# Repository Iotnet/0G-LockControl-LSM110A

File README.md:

# 0G LockControl — Alarma IoT dual (acelerómetro + magnético)

> Alarma inalámbrica compacta con detección de movimiento y apertura de puerta/ventana, comunicación Sigfox RC2 sobre el SoC LSM110A.

## Descripción

**0G LockControl** es un dispositivo electrónico autónomo que combina **dos modos de detección de eventos** y los transmite por la red **Sigfox (0G)**:

- **Movimiento / vibración** vía acelerómetro **LIS2DW12** (I²C).
- **Apertura de puerta o ventana** vía sensor magnético — **reed switch NA** o **hall DRV5032** (ambos footprints en la PCB).

El dispositivo es **event-driven**: duerme en modo Stop2 (~3 µA total) y solo despierta por interrupción de hardware. El firmware se ejecuta directamente sobre el **STM32WL** integrado en el LSM110A (firmware API, sin MCU externo).

### Características

- Comunicación **Sigfox RC2** (902-928 MHz, México) — sin WiFi ni red celular.
- Tamaño objetivo **< 5 cm** — instalación adhesiva en interior (oficina, bodega, cuarto frío).
- Batería desechable **CR2450 (3 V, 620 mAh)** + capacitor de soporte 470 µF para pulsos de TX.
- Vida útil estimada de meses a años según frecuencia de eventos.
- Costo reducido de operación y manufactura.

## Arquitectura del sistema

### Ciclo de operación

```
Sleep (3µA)  →  Wake por INT (accel o magnético)  →  Leer sensor
        →  Armar payload 12 bytes  →  TX Sigfox (~50 mA × 2 s)  →  Sleep
```

### Bloques del sistema

<details>
<summary>Ver arquitectura del sistema completo (dispositivo → Sigfox → nube → app)</summary>

</details>

<details>
<summary>Ver diagrama anterior (v1)</summary>

> Diagrama disponible también en formato vectorial: [arquitectura-producto-v1.svg](./docs/Images/arquitectura-producto-v1.svg)

</details>

### Flujo de operación

1. **Detección.** El acelerómetro o el sensor magnético genera una interrupción de hardware.
2. **Despierta.** El LSM110A sale del modo Stop2 vía EXTI.
3. **Lectura.** Se leen sensores (accel via I²C, estado del magnético).
4. **Transmisión.** Se arma el payload de 12 bytes y se envía un mensaje Sigfox.
5. **Entrega.** El backend de Sigfox ejecuta un callback HTTP hacia el servidor de la app.
6. **Notificación.** La app móvil muestra la alerta con timestamp e ID del dispositivo.

## Justificación de arquitectura y cumplimiento normativo

Este dispositivo utiliza el LSM110A con **firmware API** — el código de aplicación corre directamente dentro del STM32WL del módulo, sin MCU externo. Esta es una variante oficial ofrecida por el fabricante SJI.

**¿Por qué no se usa un MCU externo con comandos AT?**
- Menor consumo (un solo MCU en sleep vs dos)
- Menor tamaño (cumple objetivo <5cm)
- Menor costo (~$2-4 USD menos por unidad)
- Menor complejidad de firmware

**¿Se pierden certificaciones?**
No. La certificación Sigfox Verified cubre la capa de RF/protocolo, que es la misma en las versiones AT y API. Para nuestro producto final aplicaremos el enfoque modular de Sigfox Ready, que hereda la conformidad RF del módulo certificado. La FCC del módulo tampoco se afecta mientras no se modifique la capa de radio ni la antena.

Ver documento completo: [docs/arquitectura-justificacion.md](docs/arquitectura-justificacion.md)

### Certificaciones requeridas para comercialización

| Certificación | Qué cubre | Estado |
|---|---|---|
| Sigfox Verified | RF y protocolo del módulo | ✅ Heredada del LSM110A |
| Sigfox Ready | Rendimiento radiado del producto final | ☐ Post-MVP (prueba en lab acreditado) |
| FCC | Radiofrecuencia (USA) | ✅ Heredada del LSM110A (ID: 2AS8LLSM110A) |
| NOM-208 / IFT-008 | Regulación México 902-928 MHz | ☐ Post-MVP (homologación IFT) |

## Componentes principales

| Componente | Parte | Función |
|---|---|---|
| SoC + radio | **LSM110A** (STM32WLE5CC) | MCU Cortex-M4 single-core + radio Sigfox integrado |
| Acelerómetro | **LIS2DW12** (I²C) | Detección de movimiento, INT1 → PA0 |
| Sensor magnético A | **Reed switch NA** | Detección de apertura (opción A) |
| Sensor magnético B | **DRV5032** (hall) | Detección de apertura (opción B) |
| Batería | **CR2450** (3 V, 620 mAh) | Alimentación desechable |
| Cap. soporte | 470 µF electrolítico | Soporte para el pulso de TX Sigfox |
| LDO (opcional) | **TPS7A02** + bypass 0 Ω | Regulación opcional |
| Antena | Traza PCB 50 Ω | Diseño SJI (certificado FCC) |

## Plataforma de desarrollo

| Herramienta | Uso |
|---|---|
| **STM32CubeIDE** | Desarrollo de firmware (C, bare-metal) |
| **STM32CubeMX** | Configuración de periféricos y clocks |
| **KiCad** | Diseño esquemático y PCB |
| **ST-Link + SWD** | Programación y debug |
| **Sigfox Backend** | Dashboard y callbacks |

## Plan de milestones

| Milestone | Entregable | Semana |
|---|---|---|
| **M0** | Repo + spec + CubeIDE setup | 1-2 |
| **M1** | Esquemático KiCad | 2-5 |
| **M2** | FW en Nucleo (accel + reed + Sigfox) | 2-5 |
| **M3** | PCB layout + gerbers | 5-7 |
| **M4** | Low power validado en Nucleo | 7-8 |
| **M5** | PCB fabricada y ensamblada | 8-11 |
| **M6** | Integración FW en PCB custom | 11-12 |
| **M7** | Prueba de campo | 12 |

> **[Ver dashboard interactivo del plan MVP](https://jdiaznxt.github.io/0G-LockControl-LSM110A/docs/dashboard-mvp.html)** — Gantt con checklist por tarea, clic para expandir detalles.

## Estructura del repositorio

```
0G-LockControl-LSM110A/
├── Hardware/
│   ├── v0-replica-sji/    # Réplica v0 del diseño de referencia SJI
│   │   ├── ESTADO.md              # Estado entre fases: decisiones, deuda, hallazgos
│   │   ├── 00-fuente-de-verdad/   # Datos extraídos del DS/UM, con documento y página
│   │   ├── kicad-lib/             # Símbolo 34 pines + footprint LGA-34 (KiCad)
│   │   ├── 01-energia/            # F2  energía + GATE 2
│   │   ├── 02-esquematico/        # F3  esquemático (bloques/ + export/)
│   │   ├── 03-bom/                # F4  BOM
│   │   ├── 04-antena/             # F5  antena
│   │   ├── 05-layout/             # F6  layout
│   │   ├── 06-fabricacion/        # F7  fabricación
│   │   └── 07-bring-up/           # F7  bring-up (el uplink cierra v0)
│   ├── kicad/             # Proyecto KiCad (esquemático + PCB)
│   ├── Datasheets/        # Hojas de datos de componentes clave
│   ├── Schematic/
│   ├── PCB/
│   └── BOM/
├── Firmware/
│   ├── sdk/               # Fork del SDK de SJI (LSM110A)
│   ├── app/               # Código de aplicación
│   ├── drivers/           # Drivers de sensores I2C
│   ├── src/
│   ├── libs/
│   ├── config/
│   └── tools/
├── 3D-Models/
│   ├── Enclosure/
│   └── Assembly/
├── Tests/
│   ├── Lab/
│   └── Field/
├── App/
│   ├── Mobile/
│   └── Backend/
├── docs/
│   ├── spec-producto.md       # Especificación completa v1.0
│   ├── decisiones-tecnicas.md # Decisiones arquitectónicas (ADRs)
│   ├── pinout-lsm110a.md      # Asignación de pines
│   ├── Architecture/
│   ├── Images/
│   ├── References/
│   └── Guides/
├── .gitignore
└── README.md
```

## Antecedentes del desarrollo

Este proyecto es la evolución del trabajo realizado con la placa **NUCLEO-WL55JC2**, donde se validaron los siguientes hitos:

- Conexión exitosa a la red Sigfox (registro en backend, envío de mensajes).
- Conexión exitosa a LORIOT vía LoRaWAN (validación de stack).
- Implementación de detección de flanco con reed switch.
- Envío de payload Sigfox al detectar apertura.
- Caracterización del microcontrolador y periféricos del STM32WL55.

La transición al **LSM110A** permite pasar de una placa de desarrollo a un SoC integrado, habilitando el diseño de una PCB compacta y de bajo costo para producción. El firmware se programa directamente sobre el STM32WL del módulo (firmware API), sin necesidad de MCU externo ni de comandos AT.

## Protocolos de comunicación

### Sigfox (protocolo principal)

- **Zona:** RCZ2 (México / América Latina).
- **Frecuencia:** 902-928 MHz uplink.
- **Mensajes:** hasta 140 mensajes/día uplink, 4 downlink/día.
- **Payload:** máximo 12 bytes por mensaje.
- **Alcance:** hasta 50 km en zona rural, 3-10 km en zona urbana.
- **Potencia TX:** configurable, default +14 dBm (~50 mA).

### Comunicación local (futuro)

- BLE (Bluetooth Low Energy) para activación y configuración desde la app móvil.

## Documentación adicional

- 📕 **[Especificación de producto v1.0 (PDF)](./docs/References/spec-producto-lsm110a-v1.pdf)
- 📄 [Especificación de producto v1.0 (Markdown)](./docs/spec-producto.md)
- 📄 [Decisiones técnicas (ADRs)](./docs/decisiones-tecnicas.md)
- 📄 [Selección de acelerómetro — comparativa y abastecimiento](./docs/seleccion-acelerometro.md)
- 📄 [Pinout de los 34 pines (fuente de verdad, DS R08 Tabla 5-1-1)](./Hardware/v0-replica-sji/00-fuente-de-verdad/pinout-34-pines.md)
- 📄 [Asignación de pines en v0](./docs/pinout-lsm110a.md)
- 📄 [Estado de la réplica v0 del diseño SJI](./Hardware/v0-replica-sji/ESTADO.md)
- 📄 [Justificación de arquitectura API + certificaciones](./docs/arquitectura-justificacion.md)

## Empresa

**0G IoT Net Solutions** — [iotnet.mx](https://iotnet.mx)

## Desarrollador

**José Francisco Díaz Figueroa** — Embedded Systems R&D Engineer
jdiaz@iotnet.mx

## Referencias

- [Documentación STM32WL Series](https://www.st.com/en/microcontrollers-microprocessors/stm32wl-series.html)
- [Repositorio LSM110A (Support-SJI)](https://github.com/Support-SJI/LSM110A)
- [Sigfox Build — Development](https://build.sigfox.com/development)
- [Sigfox Build — Industrialization](https://build.sigfox.com/industrialization#the-sigfox-credentials)
- [STM32CubeWL GitHub](https://github.com/STMicroelectronics/STM32CubeWL)
- [RF Board Layout Guide (AN5457)](https://www.st.com/resource/en/application_note/dm00660594.pdf)

## Licencia

Por definir.

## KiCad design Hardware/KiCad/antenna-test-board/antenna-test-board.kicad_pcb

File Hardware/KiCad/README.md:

# Antena PCB en KiCad — `ANT_IFA_915MHz_LSM110A`

Diseño en KiCad de la antena IFA ranurada del plano **«1.5 Antenna Dimension»**, para el
0G LockControl (LSM110A, Sigfox RC2/RC4, **902 – 928 MHz**).

> Reconstruida y **verificada píxel a píxel contra el plano oficial** del
> `SJIT_LSM110A_UserManual_Rev1.4`. Esa banda no es una elección: el S11 medido por SJI da
> ≤ −16 dB en 902 – 928 MHz y solo −8.7 dB a 868 MHz, así que **para EU868 hay que
> reajustar**.

Todo se genera desde un único fichero de geometría paramétrica y se verifica con el motor
real de KiCad: **142 comprobaciones, 0 fallos, DRC limpio**.

---

## ⚠️ Aviso de certificación — leer antes de usarlo en producción

Este footprint es un **redibujo**. La certificación modular FCC del LSM110A
(FCC ID `2AS8LLSM110A`) cubre **únicamente el patrón «EVB_LSM ANT» de SJI**.

Dónde estamos, con precisión:

- ✅ **La geometría coincide con el plano oficial de SJI** (User Manual Rev 1.4 § 1.5),
  verificada píxel a píxel sobre el bitmap original: los seis niveles verticales, las dos
  aperturas de ranura, los extremos horizontales y el gap del CPWG. No queda ninguna cota
  en duda.
- ✅ **La red de matching coincide con el esquemático oficial** (§ 1.3): `L101` 0 Ω serie,
  `C101` 2.2 pF shunt lado antena, `C102` DNI shunt lado radio.
- ⚠️ **Lo que el plano no resuelve** es el detalle por debajo de ~0.12 mm: radios de
  esquina y compensaciones de grabado. Para eso sigue haciendo falta el **Gerber**, que es
  confidencial (pedirlo a GREATECH o SJI bajo NDA — ver
  [`certificacion-FCC/README.md`](../certificacion-FCC/README.md)).
- ⚠️ **Para apoyarse en la certificación modular**, la decisión no es de ingeniería sino
  del expediente: hay que confirmar con el certificador si «igual al plano cotado del
  fabricante» basta, o si exige el Gerber. `docs/especificaciones-diseno-pcb.md` pide lo
  segundo: *«Antena importada del Gerber oficial SJI (NO redibujada a mano)»*.
- ✅ **Hay criterio de aceptación eléctrico:** el S11 medido de SJI (§ 1.6) está en
  [`docs/verificacion.md`](docs/verificacion.md#criterio-de-aceptación-de-la-medida). Si la
  placa fabricada reproduce esa curva, el redibujo queda validado también eléctricamente.

---

## Contenido

**Las bibliotecas KiCad NO viven aquí.** Están donde vive el LSM110A, para que KiCad
necesite un solo path registrado y todo salga bajo un único nickname:

```
../v0-replica-sji/kicad-lib/                nickname de footprints: 0G-LockControl
  LSM110A.kicad_mod                         módulo LGA-34            (generado en F1)
  LSM110A.kicad_sym                         símbolo, 34 pines        (generado en F1)
  ANT_IFA_915MHz_LSM110A.kicad_mod          la antena: cobre + keepout + documentación
  ANT_LSM110A_BreakAwaySlots_EVM_ONLY.kicad_mod  troquelado del EVM - NO en el producto
  C_0402_1005Metric_0G.kicad_mod            land 0402 para L101 / C101 / C102
  TP_Coax_50R_NanoVNA.kicad_mod             isla de 3 pads para pigtail coaxial
  0G_Antenna.kicad_sym                      símbolo de la antena (2 pines: FEED, GND)
```

Los seis últimos los regenera `tools/build.sh`; los dos del LSM110A no se tocan.
Detalle de instalación y pinout en [`../v0-replica-sji/kicad-lib/README.md`](../v0-replica-sji/kicad-lib/README.md).

Lo que sí vive en esta carpeta:

```
antenna-test-board/                         placa de prueba y ajuste, 50 × 80 mm, DRC = 0
  antenna-test-board.kicad_pcb
  antenna-test-board.kicad_pro              netclases Default (0.15) y RF (1.00 / 0.15)
  antenna-test-board.kicad_dru              reglas DRC de RF
  fp-lib-table                              resuelve las bibliotecas al abrir el proyecto

tools/                                      generadores y verificadores (fuente de verdad)
docs/                                       geometría cotada y método de verificación
export/                                     renders + informe DRC (artefactos generados)
```

## Uso

### Añadir las bibliotecas a KiCad

*Preferences → Manage Footprint Libraries* y *Manage Symbol Libraries*. **Dos entradas
bastan para todo el proyecto** (LSM110A incluido):

| Tipo | Nickname | Ruta |
|---|---|---|
| Footprints | `0G-LockControl` | `${KIPRJMOD}/../Hardware/v0-replica-sji/kicad-lib` |
| Símbolos | `0G-LockControl` | `…/kicad-lib/LSM110A.kicad_sym` |
| Símbolos | `0G-Antenna` | `…/kicad-lib/0G_Antenna.kicad_sym` |

El nickname de footprints **tiene que ser `0G-LockControl`**: es el que llevan grabado los
campos `Footprint` de los dos símbolos. Si usas otro, los enlaces hay que rehacerlos a mano.

Los símbolos son dos archivos y por tanto dos nicknames — no se pueden unificar, y es mejor
así: `LSM110A.kicad_sym` está en formato KiCad 9 y `0G_Antenna.kicad_sym` en formato KiCad 7
(que KiCad 7/8/9 leen todos). **Probado con KiCad 7.0.11:** con KiCad 7 u 8 tendrás el módulo
en el PCB pero no en el esquemático — su footprint sí carga (formato 8, tolerante) y su
símbolo no (`Unable to load library`). Con KiCad 9 carga todo. Tabla completa en el
[README de `kicad-lib`](../v0-replica-sji/kicad-lib/README.md#nota-de-versión-de-kicad).

La `fp-lib-table` de `antenna-test-board/` ya trae la entrada de footprints resuelta con ruta
relativa, así que la placa de prueba se abre sin configurar nada.

### Colocar la antena en una placa

El origen del footprint es la **esquina superior izquierda del cobre**. Para reproducir el
plano en una placa cuyo borde superior esté en `y_borde`:

```
x = (ancho_placa − 39.50) / 2      ← antena centrada
y = y_borde + 4.00
```

En la placa de prueba (50 mm de ancho, borde superior en y = 0) eso da **(5.25, 4.00)**.

El footprint trae su propio *rule area* y su courtyard, así que el plano de tierra se
recorta solo y ningún componente puede caer en la zona de la antena. No hay que dibujar
el hueco a mano.

### En el esquemático

El símbolo tiene **dos pines**, y eso es deliberado:

```
                        L101 (serie)
   RFOUT (pin 33) ─────[ 0R ]───────┬──── FEED (pin 1)  ANT1
                    │               │                    GND (pin 2) ── GND
                  C102            C101                        │
                  (DNI)         (2.2 pF)                      │
                    │               │                         │
                   GND             GND ───────────────────────┘
```

Los valores son la población de referencia del User Manual FCC. Las tres posiciones
existen en la placa de prueba para poder realizar cualquier topología al ajustar.

Una IFA está unida a masa por su stub de cortocircuito, así que ese camino existe de
verdad y el esquemático debe reflejarlo. El footprint declara los pads 1 y 2 como
**net tie** (`net_tie_pad_groups`), de modo que KiCad entiende que el corto es intencional
y el DRC no lo marca.

### Regenerar y verificar

```bash
cd Hardware/KiCad/tools
./build.sh
```

Requiere KiCad ≥ 7 con los bindings de Python. Devuelve código ≠ 0 si algo falla.

**No editar a mano** los `.kicad_mod`, el `.kicad_sym` ni el `.kicad_pcb`: se generan.
Para cambiar una cota, se cambia en `tools/antenna_geometry.py` y se regenera.

## Reglas que hay que respetar al integrarla

Si no se cumplen, la antena no resuena donde se midió:

1. Borde superior de la PCB a **4.00 mm** sobre el origen del footprint.
2. Plano de tierra arrancando **exactamente** en `y = 16.03`, en ambas capas. En una IFA
   el borde del plano es parte de la antena.
3. **Cero** cobre, plano, vías o componentes por encima de ese borde, en las dos capas.
4. Costura de vías justo por debajo del borde del plano.
5. Línea RF en **CPWG 1.00 / 0.15** desde el pad de feed (User Manual FCC 5937666).
6. El plano de tierra del producto debe parecerse al de la placa de prueba. Si cambia de
   tamaño, hay que volver a ajustar.
7. En el producto final: **20 cm** mínimo antena-personas y etiquetado
   `Contains FCC ID: 2AS8LLSM110A` / `Contains IC: 25119-LSM110A` (KDB 996369 D03).

## Placa de prueba y ajuste

`antenna-test-board/` es una placa de 2 capas y **50 × 80 mm** — la PCB de referencia de
SJI que consta en el User Manual del expediente FCC. El tamaño no es arbitrario: en una
IFA el plano de tierra es el contrapeso, así que medir sobre el mismo plano de la
referencia es la única forma de que el S11 sea comparable.

Lleva la antena colocada según el plano, plano de tierra en las dos capas, línea CPWG
50 Ω, la **red de matching en π** de la referencia SJI (`L101` serie + `C101`/`C102`
shunt, tal como la da el esquemático oficial § 1.3) y una isla de 3 pads (**J1**) para soldar
un pigtail coaxial y medir con NanoVNA — J1 cumple la función del `CON101` del EVM.

El procedimiento de ajuste está en
[`docs/verificacion.md`](docs/verificacion.md#procedimiento-de-ajuste-con-nanovna).

## Documentación

- [`docs/geometria-antena.md`](docs/geometria-antena.md) — todas las cotas, cómo se
  derivan del plano, la **verificación píxel a píxel contra el plano oficial**, el
  **S11 medido** de la § 1.6, y las tres discrepancias del plano: las tres resueltas
  contra el manual (el rótulo de 4.05, la nota que ponía C101 en serie, y las ranuras
  que resultaron ser una línea de troquelado).
- [`docs/verificacion.md`](docs/verificacion.md) — qué se comprueba y cómo, los
  **9 errores** que encontró el proceso, y qué **no** cubre.

## Estado

| | |
|---|---|
| Cadena de cotas | ✅ 17/17 |
| Footprints (cargados con `pcbnew`) | ✅ 63/63 |
| Placa: DRC + cotas del cobre real | ✅ 42/42 |
| Cotejo píxel a píxel contra el plano oficial (§1.5) | ✅ todos los rasgos medibles |
| Red de matching contra el esquemático oficial (§1.3) | ✅ L101 / C101 / C102 confirmados |
| DRC de la placa de prueba | ✅ 0 violaciones, 0 pads sin conectar, 0 errores de footprint |
| Gerber oficial de SJI (detalle < 0.12 mm) | ⏳ pendiente de NDA con GREATECH |
| S11 de referencia como criterio de aceptación | ✅ §1.6 del User Manual |
| Medida de S11 | ⏳ pendiente de fabricar la placa de prueba |

Generado y verificado con KiCad 7.0.11. Formato de fichero compatible con KiCad 7/8/9.

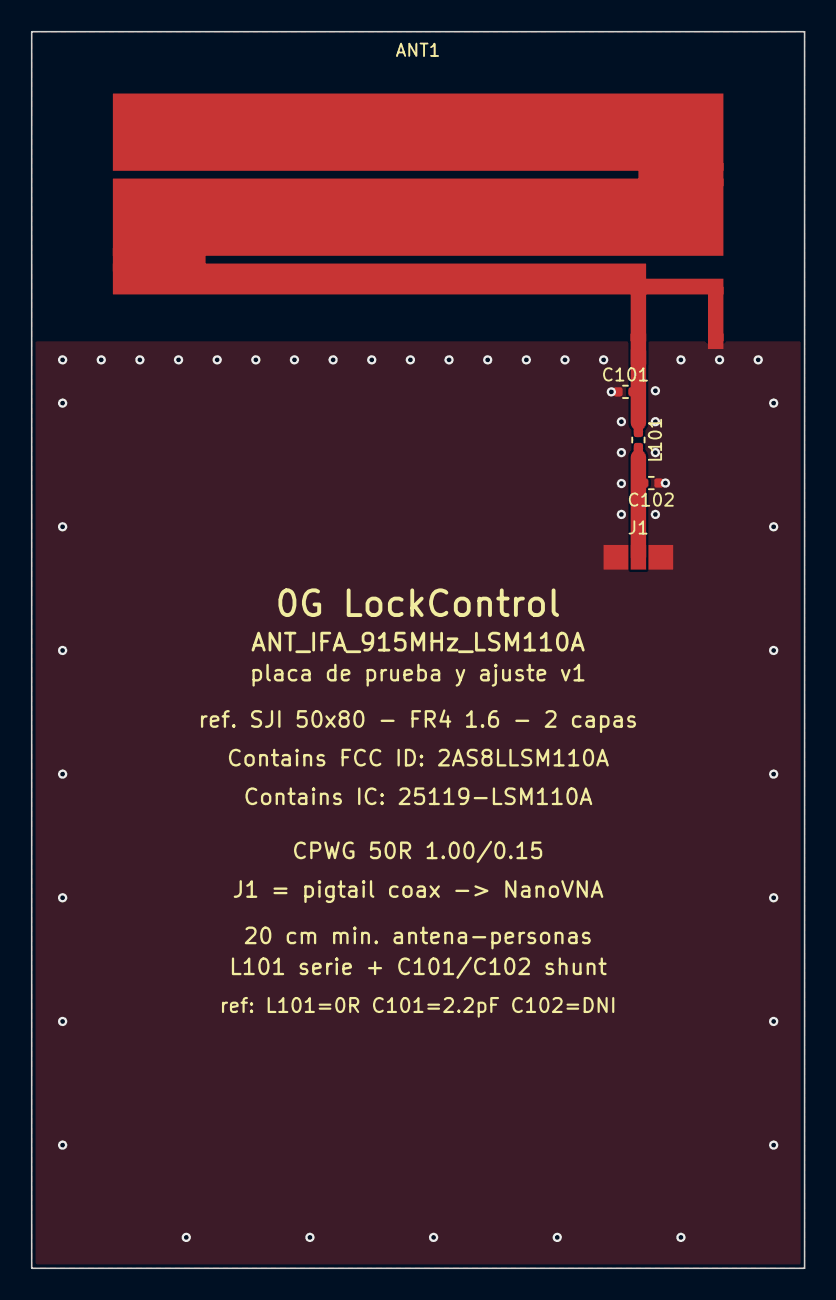
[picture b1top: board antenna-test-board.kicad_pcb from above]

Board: 2 copper layers, 50.0 x 80.0 mm, 5 parts (0 on the bottom side), 3 nets.

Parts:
ANT1: ANT_IFA_915MHz_LSM110A
C101: 2.2pF; C_0402_1005Metric_0G
C102: DNI; C_0402_1005Metric_0G
J1: 50R; TP_Coax_50R_NanoVNA
L101: 0R; C_0402_1005Metric_0G

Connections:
ANT_FEED: ANT1.1, C101.2, L101.1
GND: ANT1.2, C101.1, C102.1, J1.1, J1.3
RF_IN: C102.2, J1.2, L101.2

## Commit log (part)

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2026-05-07 feat: estructura inicial del repositorio 0G LockControl LSM110A
2026-05-07 feat: actualizar spec v1.0 - decisiones técnicas, pinout, arquitectura dual sensor
2026-05-07 feat: agrega diagrama arquitectura producto v1.0 al README y spec
2026-05-07 docs: agrega spec PDF entregable y enlace en README
2026-05-07 docs: agrega spec PDF entregable en docs/References y enlace en README
2026-05-07 Update documentation links in README.md
    Added additional documentation links in README.
2026-05-07 docs: actualiza spec PDF — quita pie de página + plan MVP a 12 semanas
2026-05-07 docs: agregar justificación de arquitectura API y plan de cumplimiento normativo
2026-05-07 Update developer title to Embedded Systems R&D Engineer
2026-05-08 docs: agregar dashboard Gantt MVP interactivo
2026-05-08 docs: agregar dashboard MVP + link en README
2026-06-01 feat: agrega aprovisionamiento Sigfox RC2 NUCLEO-WL55JC al repo
2026-06-01 docs: agrega Guia_completa NUCLEO-WL55JC + whitelist docs/Guides en gitignore
2026-06-01 docs: agrega Guia completa PDF + diagrama de flujo SVG
2026-06-02 feat(drivers): driver minimalista LIS2DW12 - WHO_AM_I + wake-up 200mg
2026-06-04 feat(hw): Add verified LSM110A footprint, rename kicad to EasyEDA
2026-06-15 docs(hardware): BOM MVP v0 verificado en LCSC (issue #4)
2026-06-15 docs(hardware): BOM MVP v0 verificado en LCSC + costos de corrida (issue #4)
2026-06-29 docs(hardware): datasheets de componentes verificados en LCSC (issue #5)
